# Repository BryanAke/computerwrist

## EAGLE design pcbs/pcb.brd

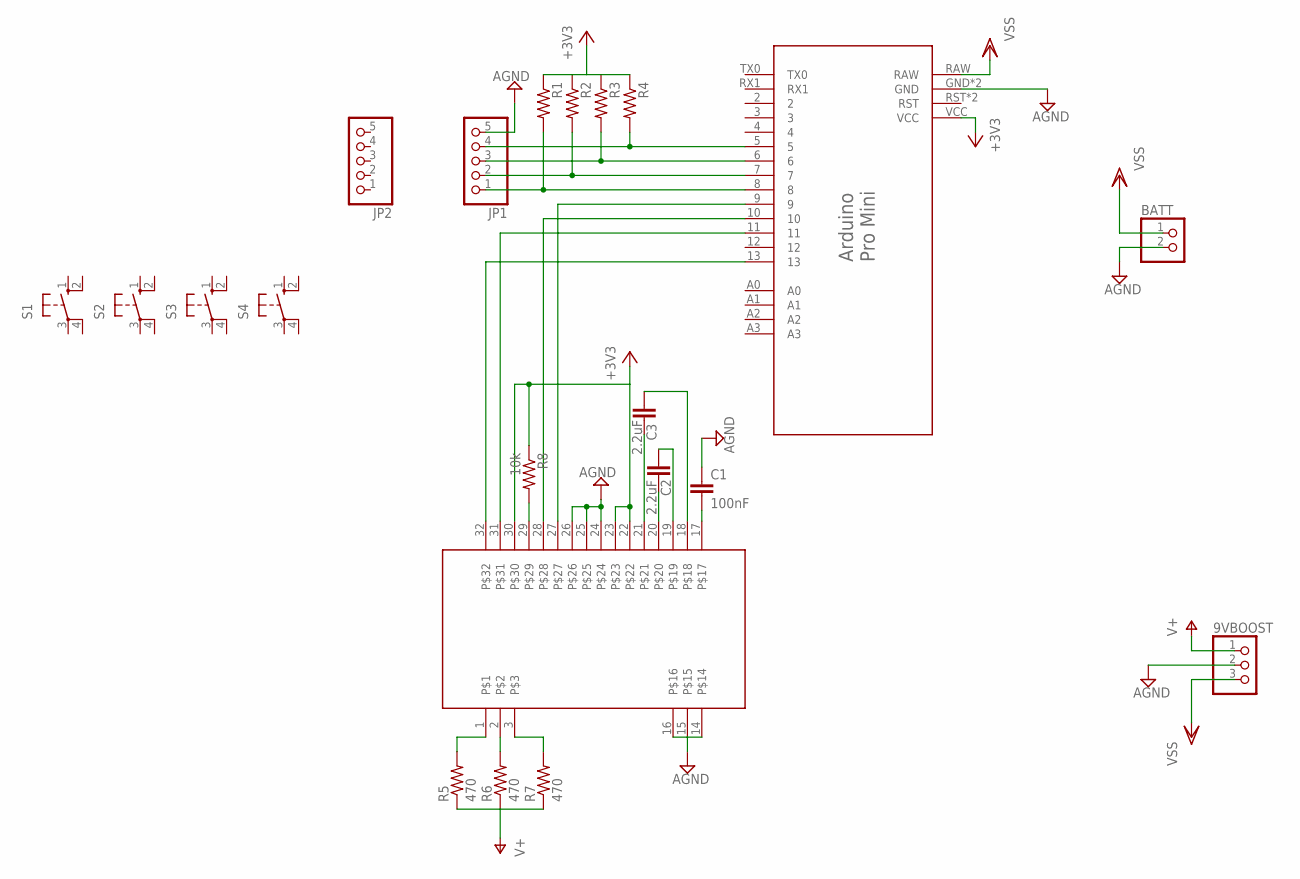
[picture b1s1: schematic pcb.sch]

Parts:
9VBOOST: PINHD-1X3; 1X03
BATT: PINHD-1X2; 1X02
C1: 100nF; C050-030X075
C2, C3: 2.2uF; C050-030X075
DOGXL160: DOGXL160-7; EA_DOGXL160-7
JP1, JP2: PINHD-1X5; 1X05
R1, R2, R3, R4: R-US_V234/12; V234/12
R5, R6, R7: 470; V234/12
R8: 10k; V234/12
S1, S2, S3, S4: 10-XX; B3F-10XX
U$1: PRO_MINI

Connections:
+3V3: DOGXL160.22, DOGXL160.23, DOGXL160.30, R1.1, R2.1, R3.1, R4.1, R8.1, U$1.VCC
AGND: 9VBOOST.2, BATT.2, C1.1, DOGXL160.14, DOGXL160.15, DOGXL160.16, DOGXL160.24, DOGXL160.25, DOGXL160.26, JP1.5, U$1.GND, U$1.GND1 (GND)
unnamed: DOGXL160.1, R5.2
unnamed: DOGXL160.2, R6.2
unnamed: DOGXL160.3, R7.2
unnamed: C2.1, DOGXL160.20
unnamed: JP1.1, R1.2, U$1.8
unnamed: JP1.2, R2.2, U$1.7
unnamed: JP1.3, R3.2, U$1.6
unnamed: JP1.4, R4.2, U$1.5
unnamed: C2.2, DOGXL160.19
unnamed: C3.1, DOGXL160.18
unnamed: C3.2, DOGXL160.21
unnamed: C1.2, DOGXL160.17
unnamed: DOGXL160.29, R8.2
unnamed: DOGXL160.27, U$1.9
unnamed: DOGXL160.28, U$1.10
unnamed: DOGXL160.31, U$1.11
unnamed: DOGXL160.32, U$1.13
V+: 9VBOOST.1, R5.1, R6.1, R7.1
VSS: 9VBOOST.3, BATT.1, U$1.RAW

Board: 2 copper layers, 21 parts (1 on the bottom side), 21 nets, no tracks yet.

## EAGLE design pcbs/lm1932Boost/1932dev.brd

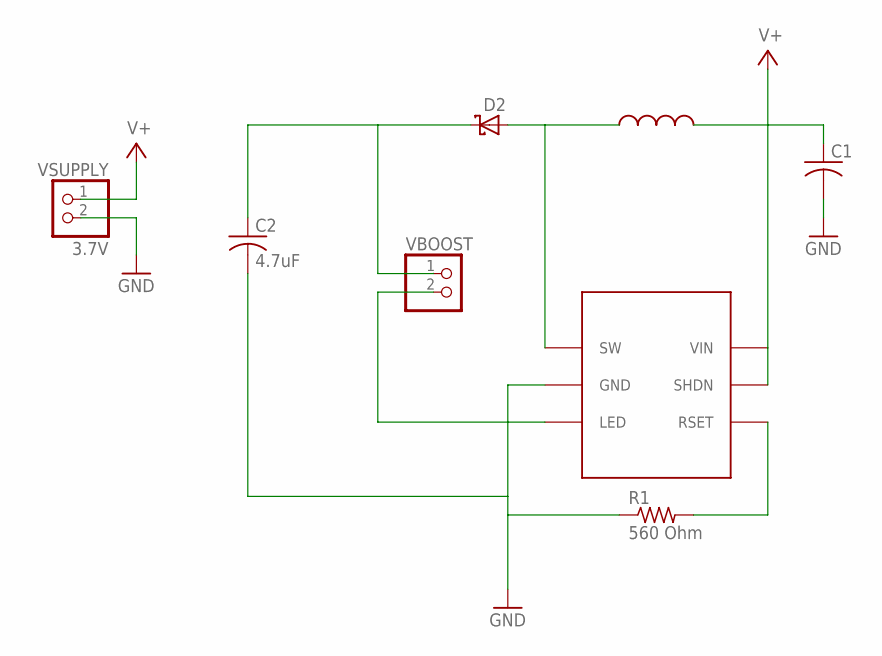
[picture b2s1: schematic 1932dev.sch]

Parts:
C1: C-USC0805; C0805
C2: 4.7uF; C0805
D2: SCHOTTKY-DIODE; SOD-323
L1: 10uH; 682C
R1: 560 Ohm; 0411V
U$1: LT1932ES; 6PIN_SOT23
VBOOST: PINHD-1X2; 1X02
VSUPPLY: 3.7V; 1X02

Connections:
GND: C1.2, C2.2, R1.1, U$1.PIN_2 (GND), VSUPPLY.2
L1: D2.A, L1.P$3 (PIN_1), U$1.PIN_1 (SW)
unnamed: U$1.PIN_3 (LED), VBOOST.2
unnamed: R1.2, U$1.PIN_4 (RSET)
unnamed: C2.1, D2.C, VBOOST.1
V+: C1.1, L1.P$4 (PIN_2), U$1.PIN_5 (SHDN), U$1.PIN_6 (VIN), VSUPPLY.1

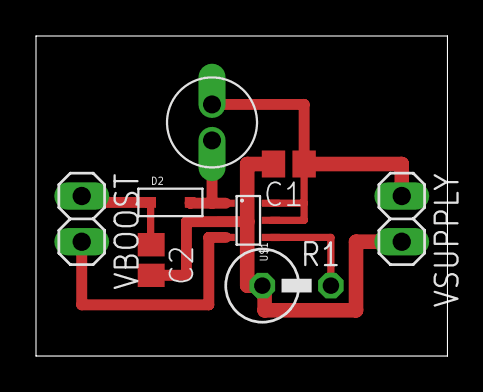
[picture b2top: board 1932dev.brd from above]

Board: 2 copper layers, 22.9 x 17.8 mm, 8 parts (0 on the bottom side), 6 nets.

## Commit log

2013-05-13 initial commit, just a copy of the dropbox folder. Might as well get this all under control while it's all simle and stuff.
2013-05-13 finished alphabet on Bw.png, started organizing repo.
2013-05-13 mockup of main screen, and some updates to the alphabet page.
2013-05-15 added keenOS folder for arduino project, using ino to build and deploy. Added u8glib to lib folder.
2013-05-15 adding bdf2u8g program.
2013-05-17 started casing design using alibre design. dimensional data in screenshots/dimensional.png.
2013-05-17 adding bdf fonts, based on screenshots from game. keentitle only includes letters for Main Menu, keen.bdf includes all alphabet upper+lower+numbers.
2013-05-17 converted to c files from bdf. Also, moved into fonts folder for organizational purposes.
2013-05-17 apparently forgot to commit spaces in keentitle.bdf
2013-05-17 adding *~ to .gitignore, to avoid saving temp files from gedit. Added ino.ini, with build targets and upload info.
2013-05-17 displays the main screen. Lookin' sweet.
2013-05-18 fixed some font issues (width of lower-case o, height of t), and wrote function for drawing header (parameterized input, draws lines around text)
2013-05-18 added input pins. Hooked up to dev input board for testing purposes, with external pull-up resistors. test print value in draw function to show value of pin5.
2013-05-18 something resembling a menu - next up, patterning the loop function after the menu example - will likely be more responsive then.
2013-05-18 menu up/down stuff added from menu example.. much more responsive.
2013-05-18 attempt at starting the whole struct thing. Not going super well.
2013-05-18 struct working, in one file. We'll seperate later.
2013-05-18 added 'back' element to struct, to hold where left button will return you to when using a menu.
2013-05-19 more work on menu structs and tracking current mode.
2013-05-26 staring to try and figure out this whole C++ thing. Future generations, judge me not by my sloppy header files.
2013-05-28 multi-menus working. Still some header file mess, and some business with organization to sort out, but getting there.
2013-05-28 updated keentitle to include the necessary letters for all the official menus.
2013-05-28 missed the W.
2013-05-28 got some menus all up in here. Most of the basics are in there. Needs some work on special stuff and the Load menu and stuff.
2013-06-05 added some smarts to menu - allows for a space in the menu as shown in the config menu, and added special rendering for centered text on a menu. Also changed scroll behavior so selector does not roll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
2013-06-06 boost circuit PCB test. In theory, this'll get the LT1932 going.
2014-01-19 adding paddle war.
2014-11-06 pcb and casing work, a bit old.
2014-11-06 openSCAD casing. bottom of casing needs adjustment, and fasteners between the two still need adding.
2015-07-15 arturo setup, and some paddlewar stuff.
2015-07-15 initial eaglecad work, and reference for pcb vertical measurements
2015-07-15 paddlewar assets.
2015-07-22 paddleWar moving stuff around.
2015-07-22 tweaking boundaries and all that
2015-07-29 platformio and teensy migration.
2015-07-29 adding platformio stuff to gitignore
2015-08-04 updated libraries to teensy compatible versions, everything compiles. Only works with sw spi.
